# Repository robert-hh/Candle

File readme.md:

# A better candle simulation

I made this little code in 2015, when I had a demand for a LED
based candle, and everything I found was either ugly
or just did not look "natural". The ugly ones are those
you get for almost no money, consisting of a battery pack
and a flicker LED, which switches brightness in a few
steps in fast random times.

So I made this one, based on a Attiny85 which replays
short sequences of brightness variations which I captured
from a real candle. I captured the brightness at a rate
of 10 samples/sec, and the code plays 30 samples/sec,
calculating the interim steps between each captured 
value. 
The repository contains a few captured data sets. Each
data set contains 16 sequences of different length, which
are replayed in random order.

Besides that, the code has two additional functions:

- It checks the voltage of the battery, which in my
case is a Li-Ion type. Below ~2.8 the controller 
gets into sleep mode. That saves the battery from 
damage. The sleep current is below 1 µA.
- You can connect a LDR to check for the environmental
brightness. If connected, the candle will pause e.g.
during the day, saving battery power. At daytime, the
sun is much brighter that the LED.

I use it with a 700mAh rechargeable battery. At an
average current of 7mA, it lasts net for 100 hours, or
about a week, when it is off at daytime.

There are two PCB layouts included, which fit nicely 
on a CR123 battery holder. They use different form
factors of the Attiny85, DIL or SOIC. For the DIL, I
bend the pins sideways and then solder it to the surface 
of the PCB. That way, the PCB sits flat beneath the
battery holder. The circuit is protected against
inserting the battery in the wrong orientation.

For use, I take a sufficiently large candle, diameter >65mm,
let it burn down such that is has a nice shape, with a cavity
of ~2cm at the top. Then I make a hole in the bottom for the
battery holder with the PCB, connect the LED and the LDR, 
and then I'm done. The only problem with that approach is,
that wax melts in the sun. So do not expose it to direct 
sunlight. Otherwise you get candles in Salvador Dali style.
Even then, I have to replace the wax part sometimes. It gets
dirty after a while at the graveyard.

Note: If you ask, what the relation to Micropython is:
I used a PyBoard 1.0 and a LDR to capture the brightness 
pattern of a real candle, and a Python script for normalizing
the data and cutting it into appropriate segments.

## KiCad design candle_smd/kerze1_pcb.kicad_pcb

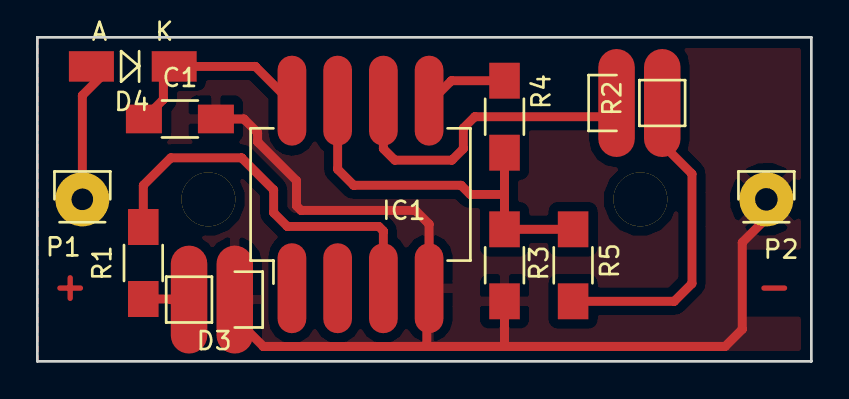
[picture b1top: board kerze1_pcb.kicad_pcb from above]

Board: 2 copper layers, 43.0 x 18.0 mm, 13 parts (0 on the bottom side), 9 nets.

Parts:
 : SolderWirePad_single_2mmDrill
 #2: SolderWirePad_single_2mmDrill
C1: 10uf; C_1206_HandSoldering
D3: +LED-; Pin_Header_Straight_1x02
D4: BAT48; MiniMELF_Standard
IC1: ATTINY85-P; DIP-8_W7.62mm_LongPads
P1, P2: Pin_Header_Straight_1x01
R1: 82; R_1206_HandSoldering
R2: Photores; Pin_Header_Straight_1x02
R3: 10k; R_1206_HandSoldering
R4: 100k; R_1206_HandSoldering
R5: 27k; R_1206_HandSoldering

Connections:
GND: C1.2, D3.1, IC1.4, P2.1, R3.2
unnamed: D3.2, R1.1
unnamed: D4.2, P1.1
unnamed: IC1.3, R1.2
unnamed: IC1.5, R4.1
unnamed: IC1.6, R2.1
unnamed: IC1.7, R3.1, R4.2, R5.2
unnamed: R2.2, R5.1
VCC: C1.1, D4.1, IC1.8

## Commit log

2020-02-06 candle: Just another candle simulation
    Based on a Attiny, to be supplied with a LiPo battery,
    with battery protection.
    The light pattern looks natural, by replaying the light
    from a real candle.
2020-02-07 readme.md: Add a note about the relation to Python
2020-02-07 candle.ino: Enforce consistent formatting using astyle
2020-02-08 tools: Files used for creating the creating the create_tables
    analogread.py was used to capture the raw brightness table
    with a PyBoard 1.0
    create_tables creates the data header file from a list of brightness
    values.
2022-09-21 candle: A better candle simulation.
    Based on a Attiny, to be supplied with a LiPo battery,
    with battery protection.
    The light pattern looks natural, by replaying the light
    from a real candle.
2022-09-21 candle: Change the default data file.
